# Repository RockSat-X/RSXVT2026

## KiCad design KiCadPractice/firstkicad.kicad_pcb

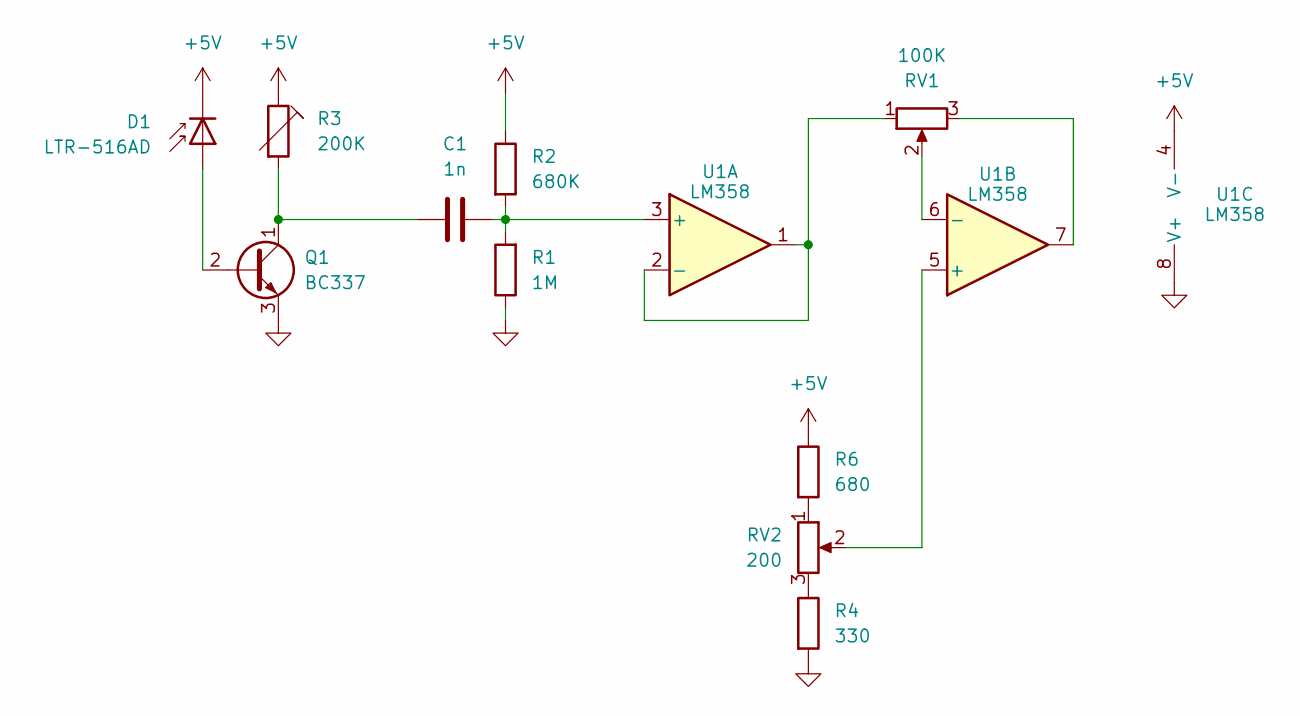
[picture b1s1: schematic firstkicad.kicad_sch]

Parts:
C1: 1n; C_1206_3216Metric_Pad1.33x1.80mm_HandSolder
D1: LTR-516AD
Q1: BC337; TO-92L_Inline
R1: 1M; R_1206_3216Metric_Pad1.30x1.75mm_HandSolder
R2: 680K; R_1206_3216Metric_Pad1.30x1.75mm_HandSolder
R3: 200K; R_1206_3216Metric_Pad1.30x1.75mm_HandSolder
R4: 330; R_1206_3216Metric_Pad1.30x1.75mm_HandSolder
R6: 680; R_1206_3216Metric_Pad1.30x1.75mm_HandSolder
RV1: 100K; Potentiometer_Bourns_3266W_Vertical
RV2: 200; Potentiometer_Bourns_3266W_Vertical
U1: LM358; SOT-23-8_Handsoldering

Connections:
+5V: D1.1 (K), R2.1, R3.1, R6.1, U1.4 (V-)
GND: Q1.3 (E), R1.1, R4.2, U1.8 (V+)
unnamed: D1.2 (A), Q1.2 (B)
unnamed: C1.1, Q1.1 (C), R3.2
unnamed: R4.1, RV2.3
unnamed: R6.2, RV2.1
unnamed: RV1.3, U1.7
unnamed: C1.2, R1.2, R2.2, U1.3 (+)
unnamed: RV1.1, U1.1, U1.2 (-)
unnamed: RV2.2, U1.5 (+)
unnamed: RV1.2, U1.6 (-)

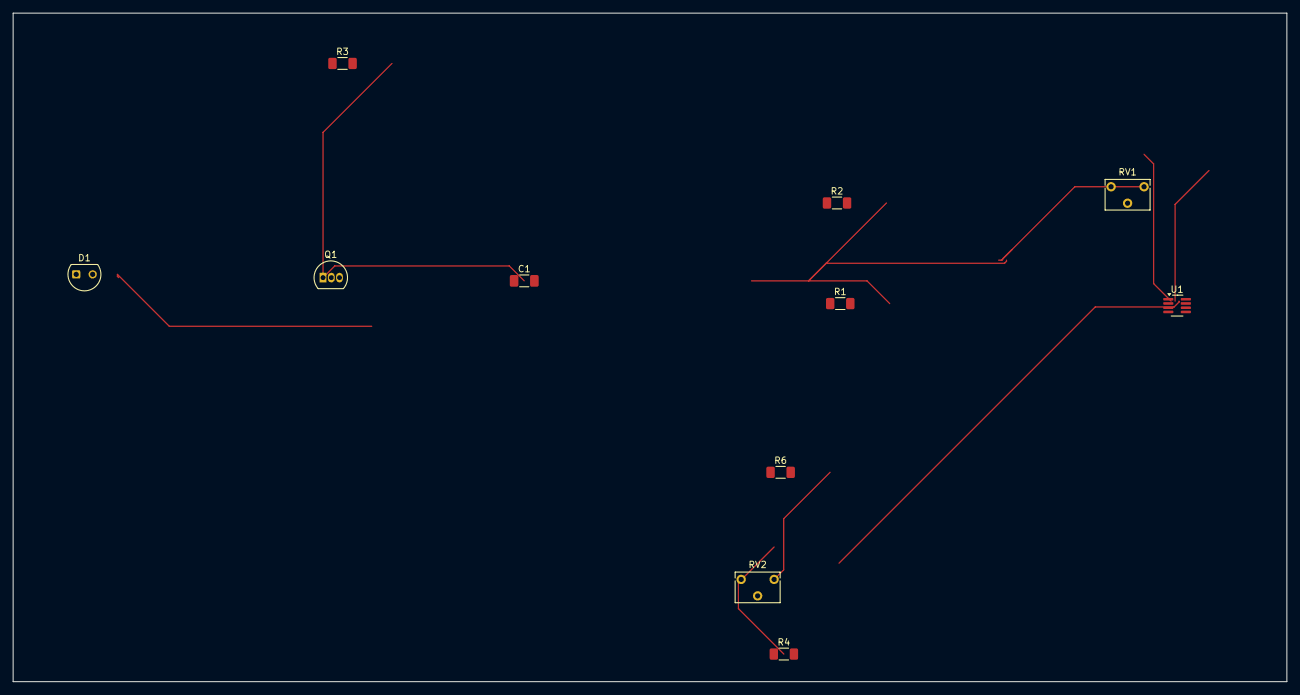
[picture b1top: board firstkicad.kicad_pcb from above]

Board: 2 copper layers, 196.2 x 103.0 mm, 11 parts (0 on the bottom side), 11 nets.

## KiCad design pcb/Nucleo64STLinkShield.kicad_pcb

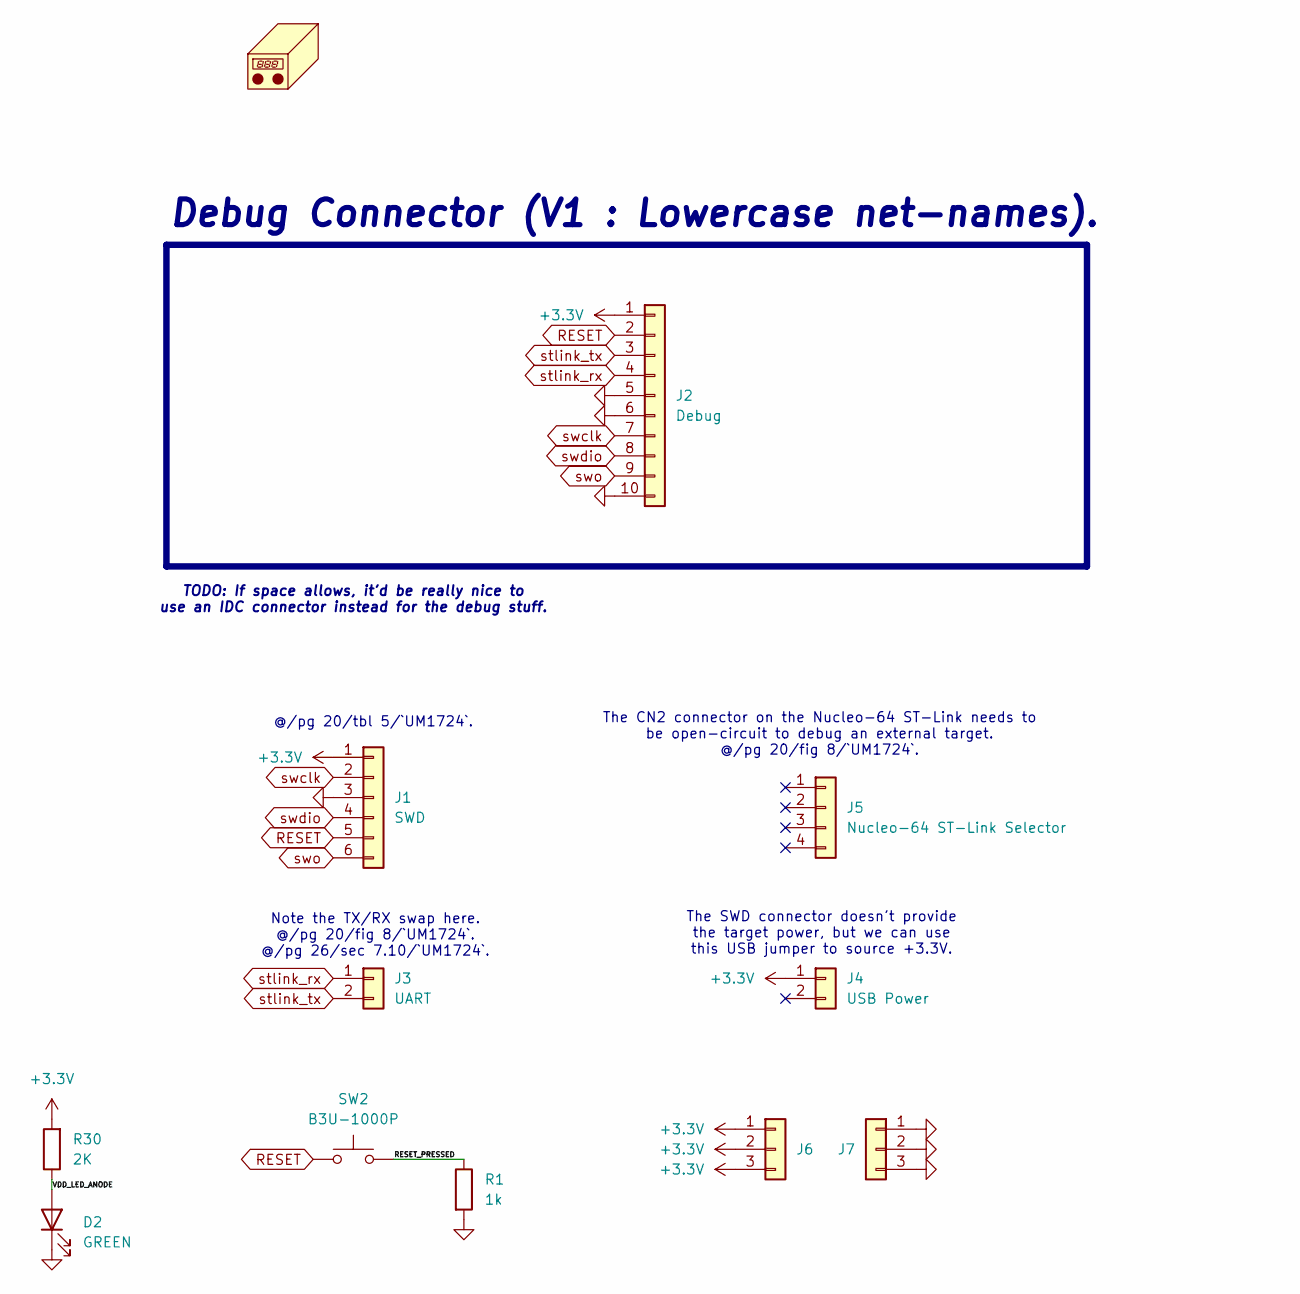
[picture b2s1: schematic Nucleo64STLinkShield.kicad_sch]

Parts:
D2: GREEN; LED_1206_3216Metric_Pad1.42x1.75mm_HandSolder
J1: SWD; PinSocket_1x06_P2.54mm_Vertical
J2: Debug; Molex_PicoBlade_53047-1010_1x10_P1.25mm_Vertical
J3: UART; PinSocket_1x02_P2.54mm_Vertical
J4: USB Power; PinSocket_1x02_P2.54mm_Vertical
J5: Nucleo-64 ST-Link Selector; PinSocket_1x04_P2.54mm_Vertical
J6, J7: Conn_01x03; PinHeader_1x03_P2.54mm_Vertical
N1: Housing; Nucleo64STLinkShieldHousing
R1: 1k; R_1206_3216Metric_Pad1.30x1.75mm_HandSolder
R30: 2K; R_1206_3216Metric_Pad1.30x1.75mm_HandSolder
SW2: B3U-1000P; SW_SPST_B3U-1000P

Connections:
+3.3V: J1.1, J2.1, J4.1, J6.1, J6.2, J6.3, R30.2
/RESET_PRESSED: R1.1, SW2.1
/VDD_LED_ANODE: D2.2 (A), R30.1
GND: D2.1 (K), J1.3, J2.5, J2.6, J2.10, J7.1, J7.2, J7.3, R1.2
RESET: J1.5, J2.2, SW2.2
stlink_rx: J2.4, J3.1
stlink_tx: J2.3, J3.2
swclk: J1.2, J2.7
swdio: J1.4, J2.8
swo: J1.6, J2.9

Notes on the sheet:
The CN2 connector on the Nucleo-64 ST-Link needs to be open-circuit to debug an external target. @/pg 20/fig 8/`UM1724`.
Debug Connector (V1 : Lowercase net-names).
Note the TX/RX swap here. @/pg 20/fig 8/`UM1724`. @/pg 26/sec 7.10/`UM1724`.
The SWD connector doesn't provide the target power, but we can use this USB jumper to source +3.3V.
TODO: If space allows, it'd be really nice to use an IDC connector instead for the debug stuff.
@/pg 20/tbl 5/`UM1724`.

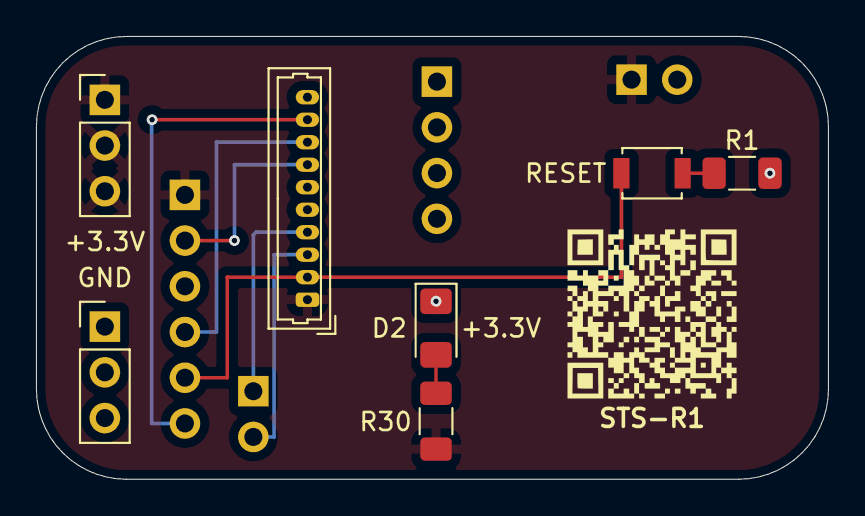
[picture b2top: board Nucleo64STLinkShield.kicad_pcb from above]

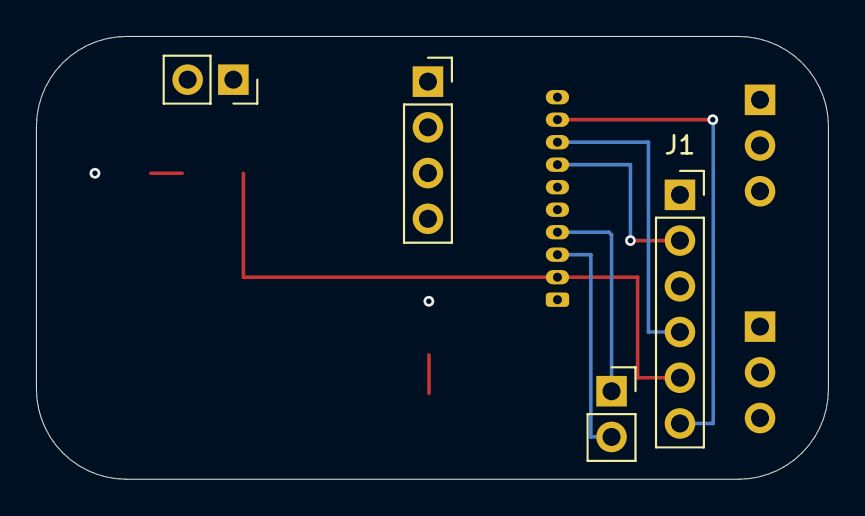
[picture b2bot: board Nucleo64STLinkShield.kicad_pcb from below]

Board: 4 copper layers, 44.0 x 24.6 mm, 12 parts (4 on the bottom side), 10 nets.

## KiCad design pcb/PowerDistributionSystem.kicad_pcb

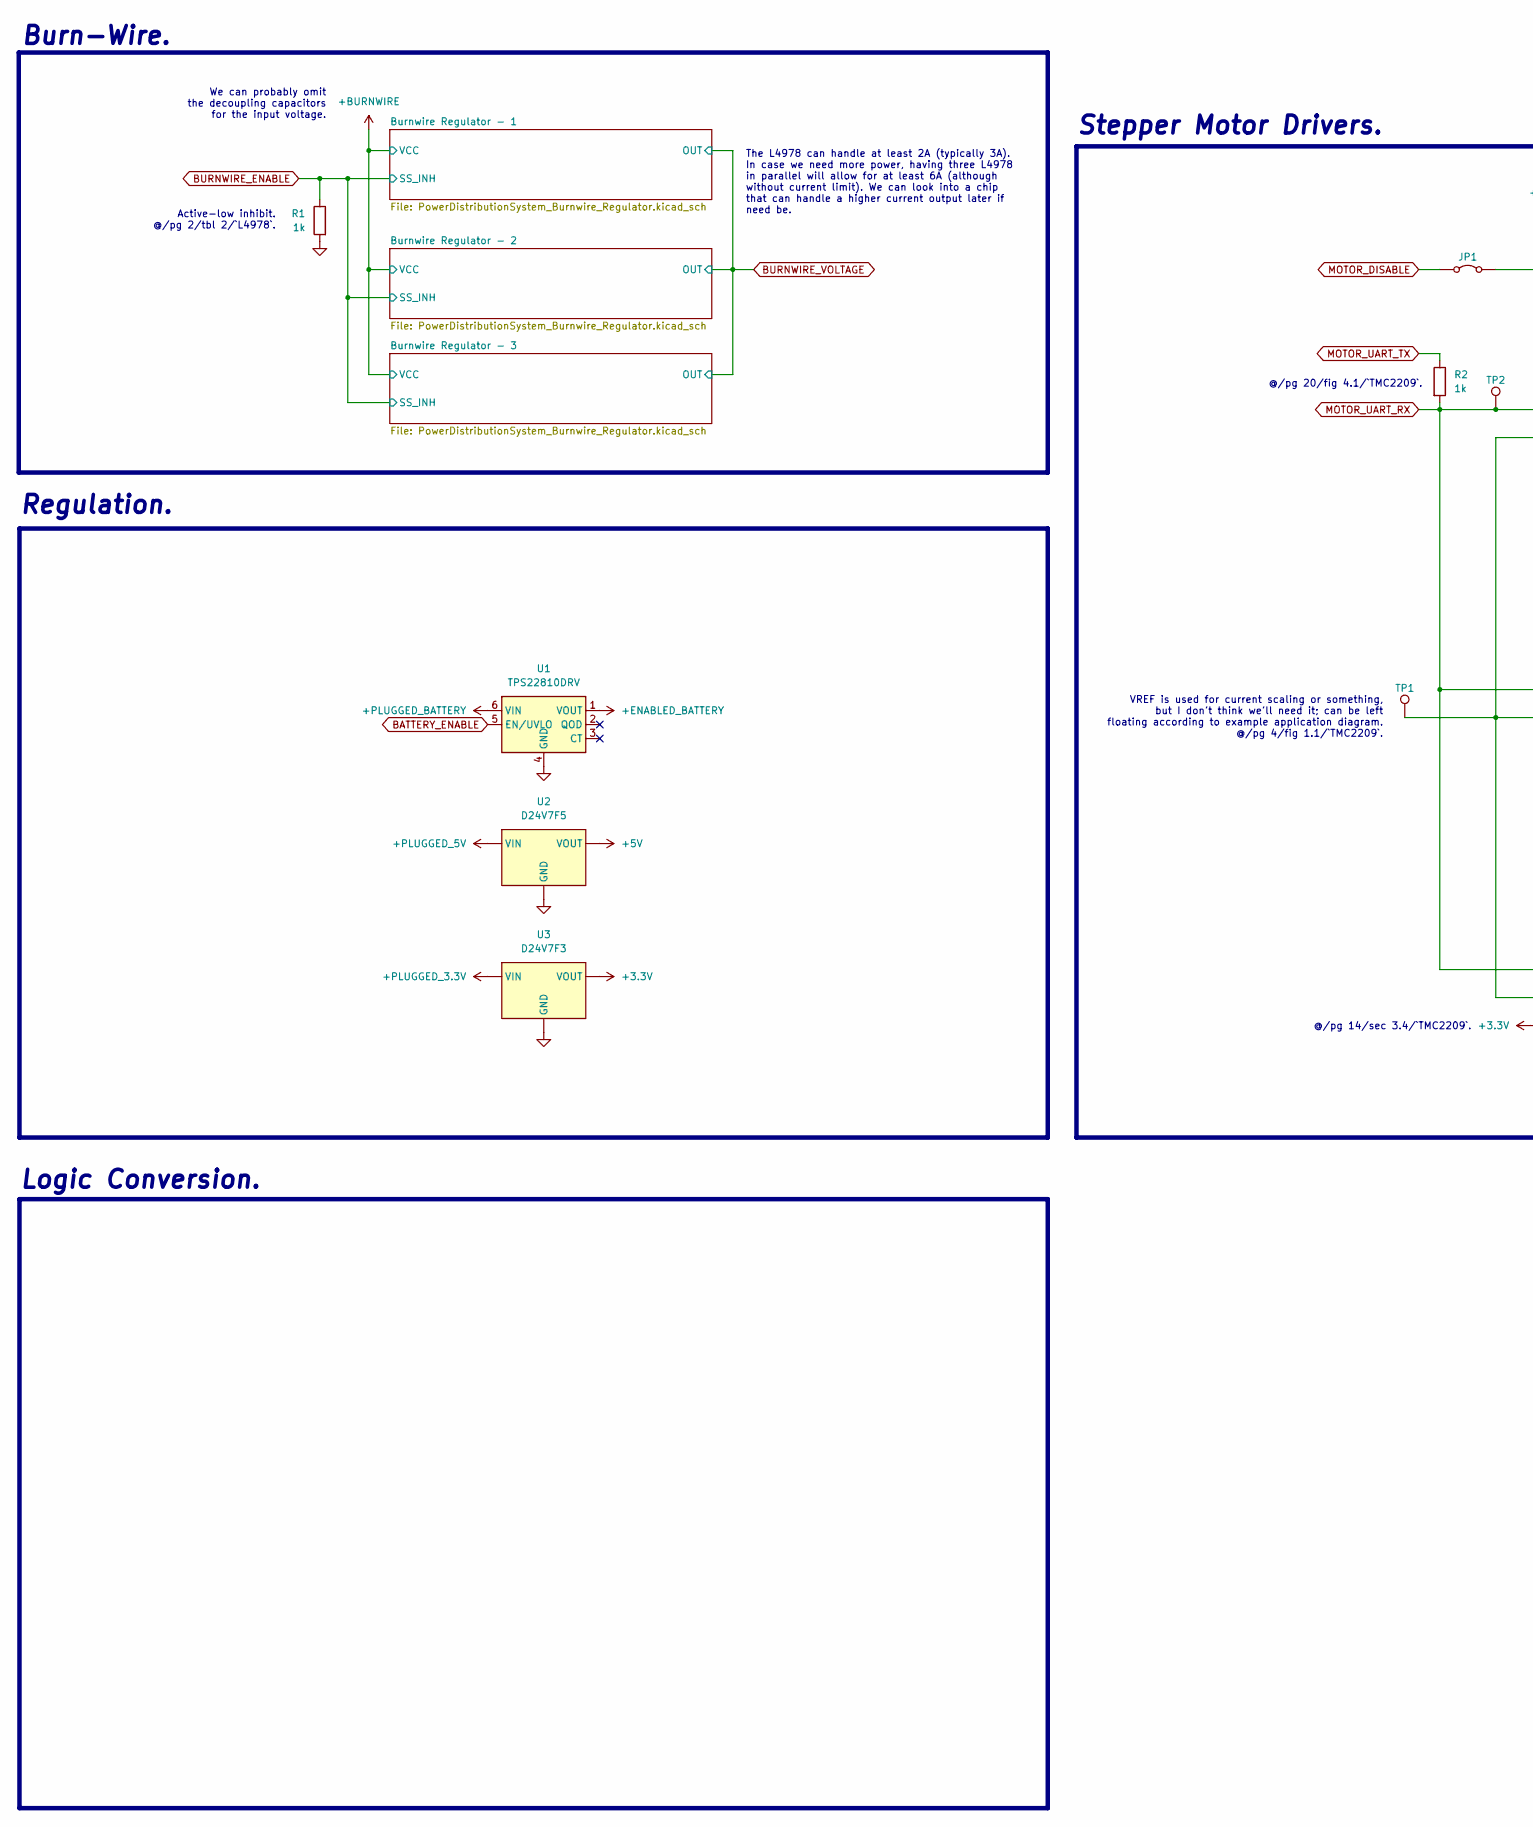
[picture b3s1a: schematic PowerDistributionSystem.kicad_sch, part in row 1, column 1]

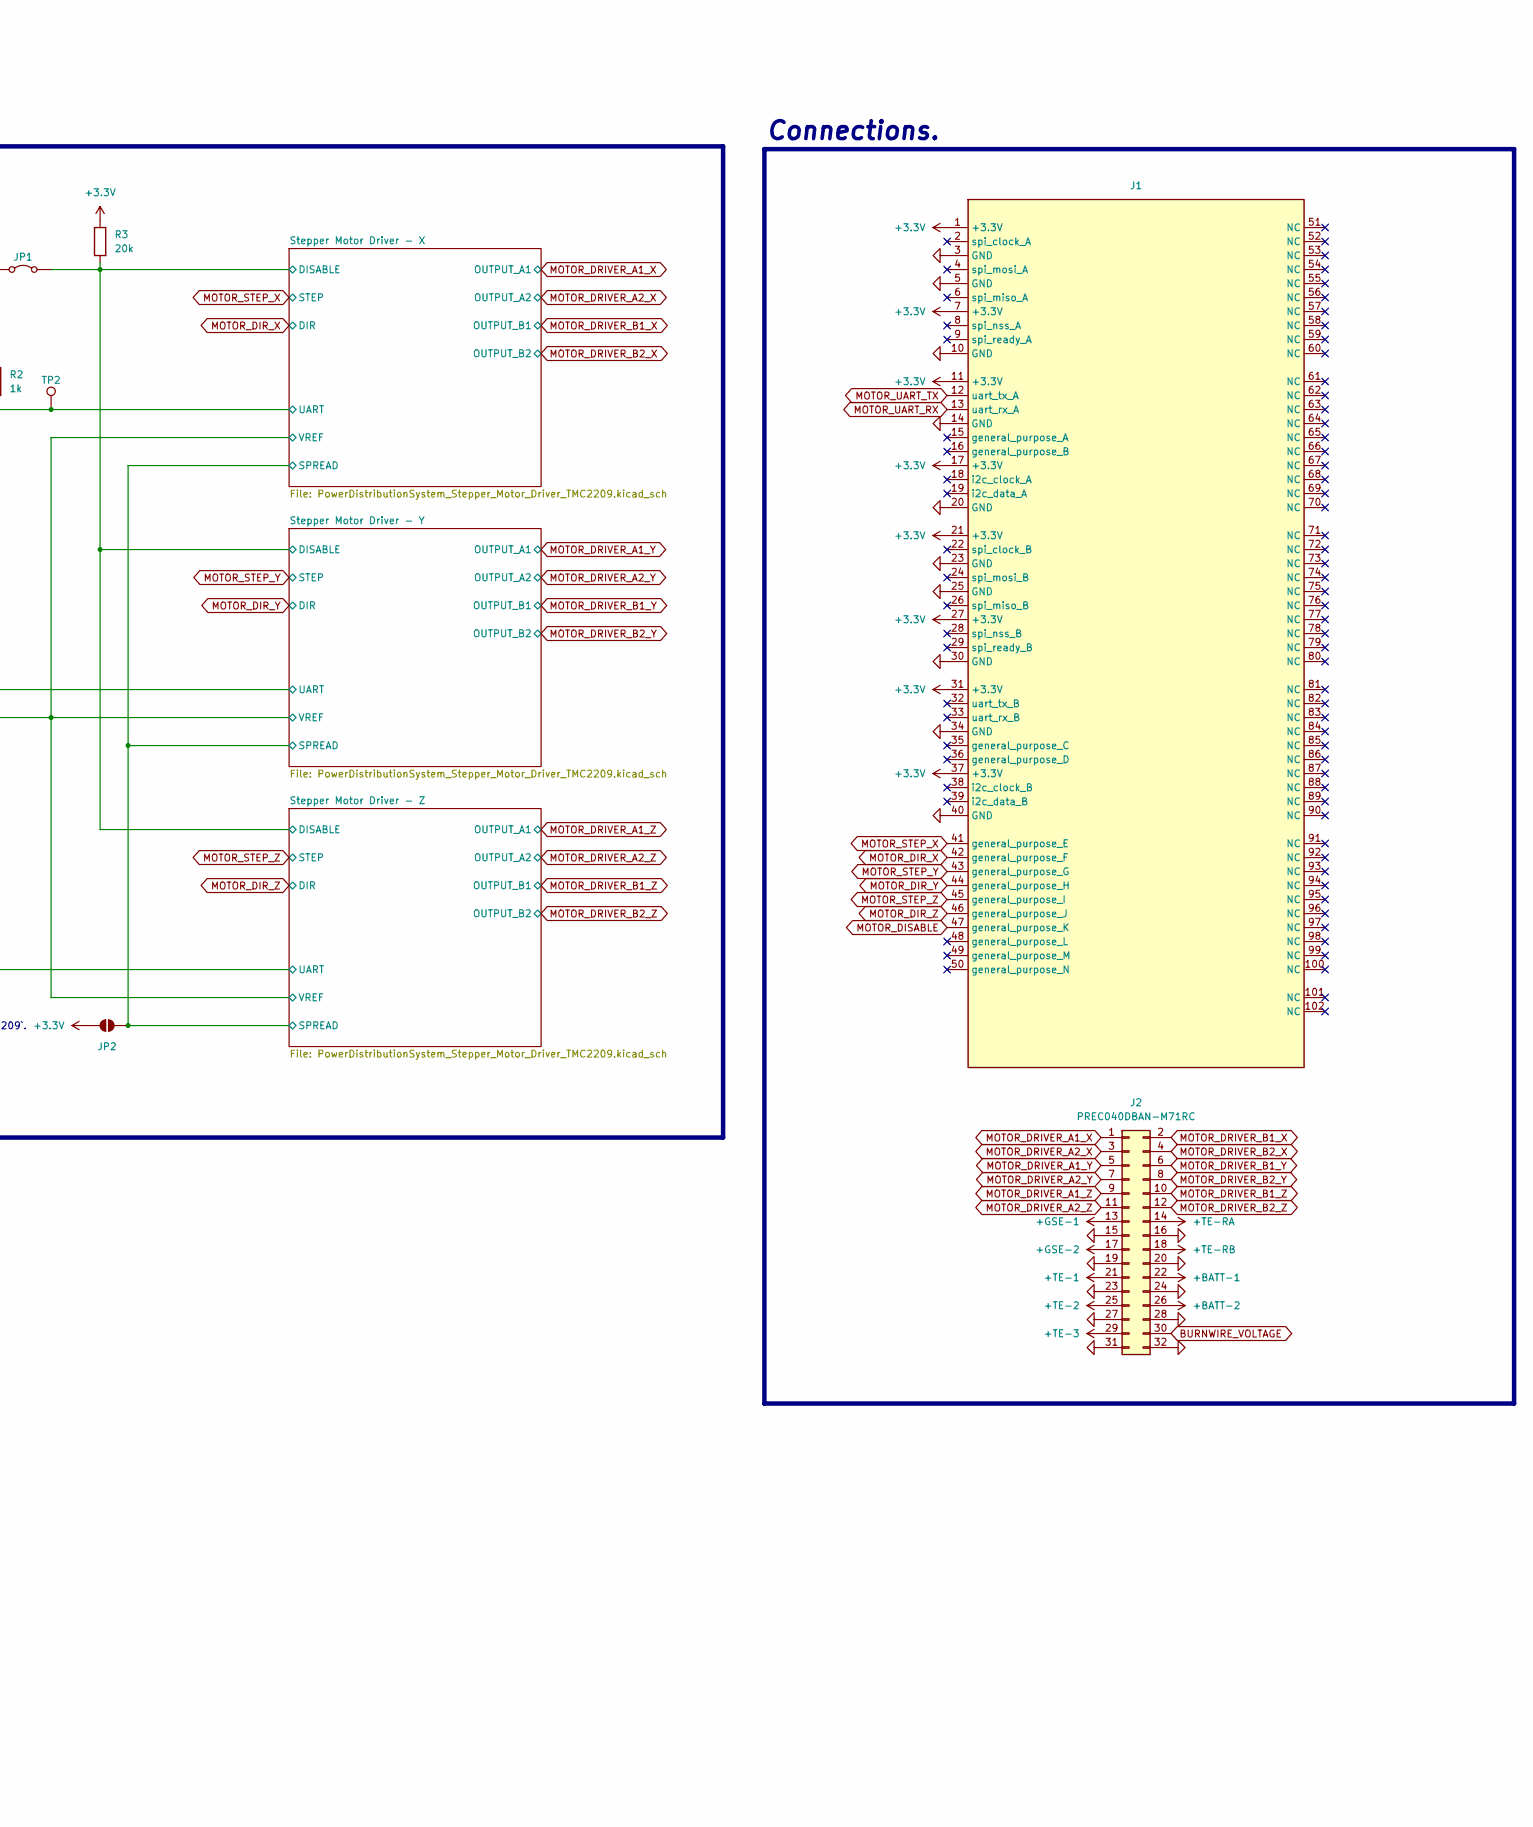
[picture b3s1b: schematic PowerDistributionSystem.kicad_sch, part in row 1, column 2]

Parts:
J1: StackConnector
J2: PREC040DBAN-M71RC; PinHeader_2x16_P2.54mm_Horizontal
JP1: Jumper_2_Bridged; SolderJumper-2_P1.3mm_Open_RoundedPad1.0x1.5mm
JP2: SolderJumper_2_Open; SolderJumper-2_P1.3mm_Open_RoundedPad1.0x1.5mm
R1, R2: 1k; R_1206_3216Metric_Pad1.30x1.75mm_HandSolder
R3: 20k; R_1206_3216Metric_Pad1.30x1.75mm_HandSolder
TP1, TP2: TestPoint; TestPoint_Pad_1.0x1.0mm
U1: TPS22810DRV; WSON-6-1EP_2x2mm_P0.65mm_EP1x1.6mm
U2: D24V7F5; D24V7Fx
U3: D24V7F3; D24V7Fx

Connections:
+3.3V: J1.1 (+3.3V), J1.7 (+3.3V), J1.11 (+3.3V), J1.17 (+3.3V), J1.21 (+3.3V), J1.27 (+3.3V), J1.31 (+3.3V), J1.37 (+3.3V), JP2.1 (A), R3.1, U3.VOUT; also elsewhere on the board
+5V: U2.VOUT
+BATT-1: J2.22
+BATT-2: J2.26
+ENABLED_BATTERY: U1.1 (VOUT)
+GSE-1: J2.13
+GSE-2: J2.17
+PLUGGED_3.3V: U3.VIN
+PLUGGED_5V: U2.VIN
+PLUGGED_BATTERY: U1.6 (VIN)
+TE-1: J2.21
+TE-2: J2.25
+TE-3: J2.29
+TE-RA: J2.14
+TE-RB: J2.18
/Stepper Motor Driver - X/DISABLE: JP1.2 (B), R3.2; also elsewhere on the board
/Stepper Motor Driver - X/SPREAD: JP2.2 (B); also elsewhere on the board
/Stepper Motor Driver - X/VREF: TP1.1; also elsewhere on the board
BATTERY_ENABLE: U1.5 (EN/UVLO)
BURNWIRE_ENABLE: R1.1; also elsewhere on the board
BURNWIRE_VOLTAGE: J2.30; also elsewhere on the board
GND: J1.3 (GND), J1.5 (GND), J1.10 (GND), J1.14 (GND), J1.20 (GND), J1.23 (GND), J1.25 (GND), J1.30 (GND), J1.34 (GND), J1.40 (GND), J2.15, J2.16, J2.19, J2.20, J2.23, J2.24, J2.27, J2.28, J2.31, J2.32, R1.2, U1.4 (GND), U1.7 (GND), U2.GND, U3.GND; also elsewhere on the board
MOTOR_DIR_X: J1.42 (general_purpose_F); also elsewhere on the board
MOTOR_DIR_Y: J1.44 (general_purpose_H); also elsewhere on the board
MOTOR_DIR_Z: J1.46 (general_purpose_J); also elsewhere on the board
MOTOR_DISABLE: J1.47 (general_purpose_K), JP1.1 (A)
MOTOR_DRIVER_A1_X: J2.1; also elsewhere on the board
MOTOR_DRIVER_A1_Y: J2.5; also elsewhere on the board
MOTOR_DRIVER_A1_Z: J2.9; also elsewhere on the board
MOTOR_DRIVER_A2_X: J2.3; also elsewhere on the board
MOTOR_DRIVER_A2_Y: J2.7; also elsewhere on the board
MOTOR_DRIVER_A2_Z: J2.11; also elsewhere on the board
MOTOR_DRIVER_B1_X: J2.2; also elsewhere on the board
MOTOR_DRIVER_B1_Y: J2.6; also elsewhere on the board
MOTOR_DRIVER_B1_Z: J2.10; also elsewhere on the board
MOTOR_DRIVER_B2_X: J2.4; also elsewhere on the board
MOTOR_DRIVER_B2_Y: J2.8; also elsewhere on the board
MOTOR_DRIVER_B2_Z: J2.12; also elsewhere on the board
MOTOR_STEP_X: J1.41 (general_purpose_E); also elsewhere on the board
MOTOR_STEP_Y: J1.43 (general_purpose_G); also elsewhere on the board
MOTOR_STEP_Z: J1.45 (general_purpose_I); also elsewhere on the board
MOTOR_UART_RX: J1.13 (uart_rx_A), R2.2, TP2.1; also elsewhere on the board
MOTOR_UART_TX: J1.12 (uart_tx_A), R2.1

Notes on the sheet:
Active-low inhibit. @/pg 2/tbl 2/`L4978`.
Connections.
The L4978 can handle at least 2A (typically 3A). In case we need more power, having three L4978 in parallel will allow for at least 6A (although without current limit). We can look into a chip that can handle a higher current output later if need be.
Burn-Wire.
Regulation.
We can probably omit the decoupling capacitors for the input voltage.
@/pg 20/fig 4.1/`TMC2209`.
Logic Conversion.
Stepper Motor Drivers.
VREF is used for current scaling or something, but I don't think we'll need it; can be left floating according to example application diagram. @/pg 4/fig 1.1/`TMC2209`.
@/pg 14/sec 3.4/`TMC2209`.

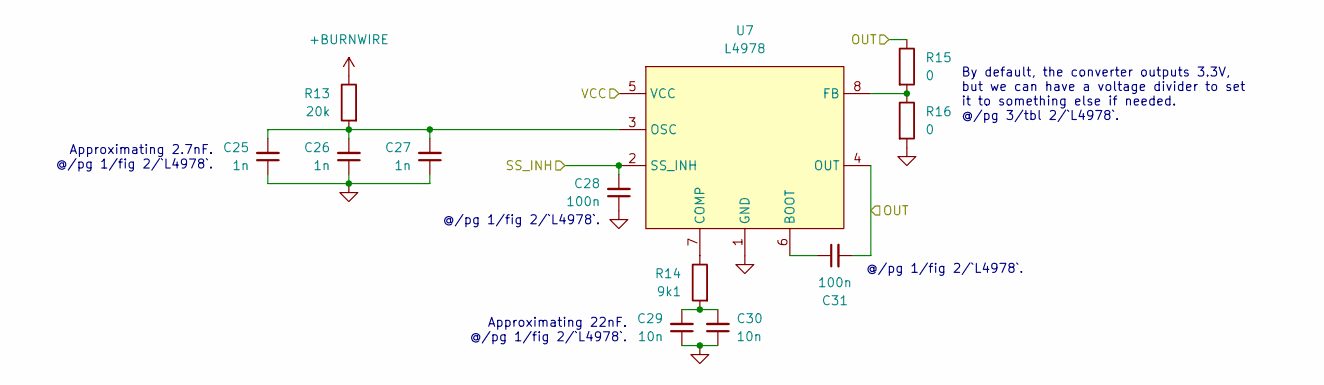
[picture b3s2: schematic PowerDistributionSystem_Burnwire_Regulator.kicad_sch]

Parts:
C25, C26, C27: 1n; C_1206_3216Metric_Pad1.33x1.80mm_HandSolder
C28, C31: 100n; C_1206_3216Metric_Pad1.33x1.80mm_HandSolder
C29, C30: 10n; C_1206_3216Metric_Pad1.33x1.80mm_HandSolder
R13: 20k; R_1206_3216Metric_Pad1.30x1.75mm_HandSolder
R14: 9k1; R_1206_3216Metric_Pad1.30x1.75mm_HandSolder
R15, R16: 0; R_1206_3216Metric_Pad1.30x1.75mm_HandSolder
U7: L4978; DIP-8_W7.62mm

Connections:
+BURNWIRE: R13.1, U7.5 (VCC); also elsewhere on the board
BURNWIRE_ENABLE: C28.2, U7.2 (SS_INH); also elsewhere on the board
BURNWIRE_VOLTAGE: C31.2, R15.1, U7.4 (OUT); also elsewhere on the board
GND: C25.1, C26.1, C27.1, C28.1, C29.1, C30.1, R16.2, U7.1 (GND); also elsewhere on the board
unnamed: C29.2, C30.2, R14.2
unnamed: C31.1, U7.6 (BOOT)
unnamed: R14.1, U7.7 (COMP)
unnamed: R15.2, R16.1, U7.8 (FB)
unnamed: C25.2, C26.2, C27.2, R13.2, U7.3 (OSC)

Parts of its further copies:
C32, C33, C34: 1n; C_1206_3216Metric_Pad1.33x1.80mm_HandSolder
C35, C38: 100n; C_1206_3216Metric_Pad1.33x1.80mm_HandSolder
C36, C37: 10n; C_1206_3216Metric_Pad1.33x1.80mm_HandSolder
R17: 20k; R_1206_3216Metric_Pad1.30x1.75mm_HandSolder
R18: 9k1; R_1206_3216Metric_Pad1.30x1.75mm_HandSolder
R19, R20: 0; R_1206_3216Metric_Pad1.30x1.75mm_HandSolder
U8: L4978; DIP-8_W7.62mm

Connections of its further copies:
+BURNWIRE: R17.1, U8.5 (VCC); also elsewhere on the board
BURNWIRE_ENABLE: C35.2, U8.2 (SS_INH); also elsewhere on the board
BURNWIRE_VOLTAGE: C38.2, R19.1, U8.4 (OUT); also elsewhere on the board
GND: C32.1, C33.1, C34.1, C35.1, C36.1, C37.1, R20.2, U8.1 (GND); also elsewhere on the board
unnamed: C36.2, C37.2, R18.2
unnamed: C38.1, U8.6 (BOOT)
unnamed: R18.1, U8.7 (COMP)
unnamed: R19.2, R20.1, U8.8 (FB)
unnamed: C32.2, C33.2, C34.2, R17.2, U8.3 (OSC)

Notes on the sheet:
Approximating 22nF. @/pg 1/fig 2/`L4978`.
Approximating 2.7nF. @/pg 1/fig 2/`L4978`.
By default, the converter outputs 3.3V, but we can have a voltage divider to set it to something else if needed. @/pg 3/tbl 2/`L4978`.
@/pg 1/fig 2/`L4978`.

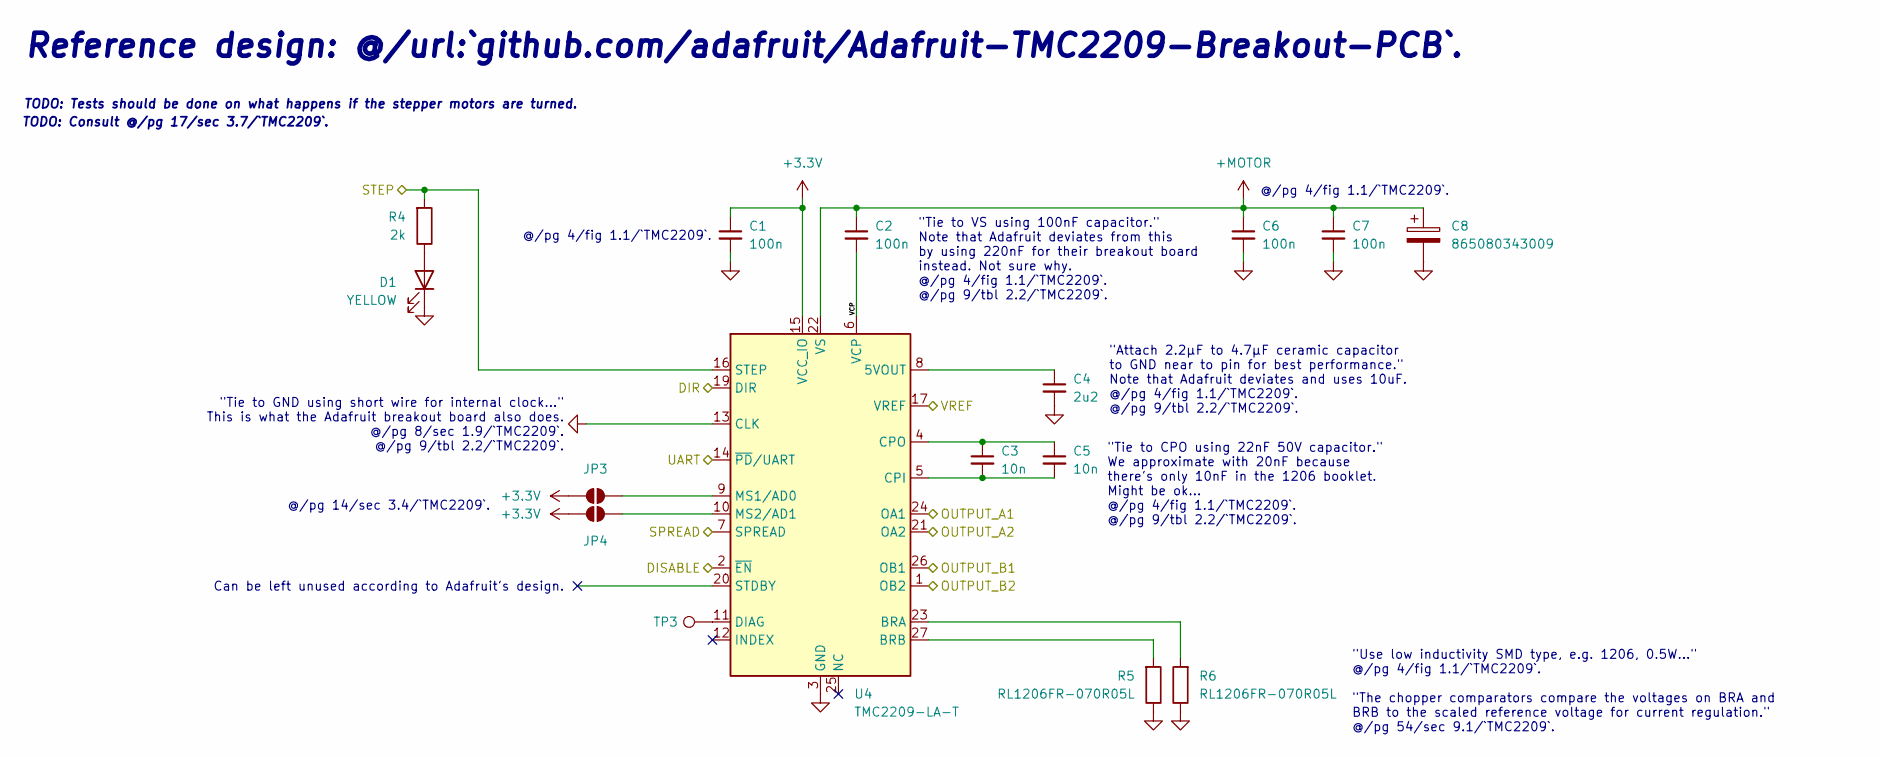
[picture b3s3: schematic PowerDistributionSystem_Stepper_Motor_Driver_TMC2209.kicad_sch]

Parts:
C1, C2, C6, C7: 100n; C_1206_3216Metric_Pad1.33x1.80mm_HandSolder
C3, C5: 10n; C_1206_3216Metric_Pad1.33x1.80mm_HandSolder
C4: 2u2; C_1206_3216Metric_Pad1.33x1.80mm_HandSolder
C8: 865080343009; CP_Elec_6.3x5.4
D1: YELLOW; LED_1206_3216Metric_Pad1.42x1.75mm_HandSolder
JP3, JP4: SolderJumper_2_Open; SolderJumper-2_P1.3mm_Open_RoundedPad1.0x1.5mm
R4: 2k; R_1206_3216Metric_Pad1.30x1.75mm_HandSolder
R5, R6: RL1206FR-070R05L; R_1206_3216Metric_Pad1.30x1.75mm_HandSolder
TP3: TestPoint; TestPoint_Pad_1.0x1.0mm
U4: TMC2209-LA-T; VQFN-28-1EP_5x5mm_P0.5mm_EP3.7x3.7mm_ThermalVias

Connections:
+3.3V: C1.1, JP3.1 (A), JP4.1 (A), U4.15 (VCC_IO); also elsewhere on the board
+MOTOR: C2.1, C6.1, C7.1, C8.1, U4.22 (VS), U4.28 (VS); also elsewhere on the board
/Stepper Motor Driver - X/DISABLE: U4.2 (~EN); also elsewhere on the board
/Stepper Motor Driver - X/SPREAD: U4.7 (SPREAD); also elsewhere on the board
/Stepper Motor Driver - X/VCP: C2.2, U4.6 (VCP)
/Stepper Motor Driver - X/VREF: U4.17 (VREF); also elsewhere on the board
GND: C1.2, C4.2, C6.2, C7.2, C8.2, D1.1 (K), R5.1, R6.1, U4.3 (GND), U4.13 (CLK), U4.18 (GND), U4.29 (GND); also elsewhere on the board
MOTOR_DIR_X: U4.19 (DIR); also elsewhere on the board
MOTOR_DRIVER_A1_X: U4.24 (OA1); also elsewhere on the board
MOTOR_DRIVER_A2_X: U4.21 (OA2); also elsewhere on the board
MOTOR_DRIVER_B1_X: U4.26 (OB1); also elsewhere on the board
MOTOR_DRIVER_B2_X: U4.1 (OB2); also elsewhere on the board
MOTOR_STEP_X: R4.2, U4.16 (STEP); also elsewhere on the board
MOTOR_UART_RX: U4.14 (~PD/UART); also elsewhere on the board
unnamed: D1.2 (A), R4.1
unnamed: JP3.2 (B), U4.9 (MS1/AD0)
unnamed: JP4.2 (B), U4.10 (MS2/AD1)
unnamed: C4.1, U4.8 (5VOUT)
unnamed: R6.2, U4.23 (BRA)
unnamed: R5.2, U4.27 (BRB)
unnamed: C3.2, C5.2, U4.5 (CPI)
unnamed: C3.1, C5.1, U4.4 (CPO)
unnamed: TP3.1, U4.11 (DIAG)

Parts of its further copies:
C9, C10, C14, C15, C17, C18, C22, C23: 100n; C_1206_3216Metric_Pad1.33x1.80mm_HandSolder
C11, C13, C19, C21: 10n; C_1206_3216Metric_Pad1.33x1.80mm_HandSolder
C12, C20: 2u2; C_1206_3216Metric_Pad1.33x1.80mm_HandSolder
C16, C24: 865080343009; CP_Elec_6.3x5.4
D2, D3: YELLOW; LED_1206_3216Metric_Pad1.42x1.75mm_HandSolder
JP5, JP6, JP7, JP8: SolderJumper_2_Open; SolderJumper-2_P1.3mm_Open_RoundedPad1.0x1.5mm
R7, R10: 2k; R_1206_3216Metric_Pad1.30x1.75mm_HandSolder
R8, R9, R11, R12: RL1206FR-070R05L; R_1206_3216Metric_Pad1.30x1.75mm_HandSolder
TP4, TP5: TestPoint; TestPoint_Pad_1.0x1.0mm
U5, U6: TMC2209-LA-T; VQFN-28-1EP_5x5mm_P0.5mm_EP3.7x3.7mm_ThermalVias

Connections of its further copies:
+3.3V: C9.1, C17.1, JP5.1 (A), JP6.1 (A), JP7.1 (A), JP8.1 (A), U5.15 (VCC_IO), U6.15 (VCC_IO); also elsewhere on the board
+MOTOR: C10.1, C14.1, C15.1, C16.1, C18.1, C22.1, C23.1, C24.1, U5.22 (VS), U5.28 (VS), U6.22 (VS), U6.28 (VS); also elsewhere on the board
/Stepper Motor Driver - X/DISABLE: U5.2 (~EN), U6.2 (~EN); also elsewhere on the board
/Stepper Motor Driver - X/SPREAD: U5.7 (SPREAD), U6.7 (SPREAD); also elsewhere on the board
/Stepper Motor Driver - X/VREF: U5.17 (VREF), U6.17 (VREF); also elsewhere on the board
/Stepper Motor Driver - Y/VCP: C10.2, U5.6 (VCP)
/Stepper Motor Driver - Z/VCP: C18.2, U6.6 (VCP)
GND: C9.2, C12.2, C14.2, C15.2, C16.2, C17.2, C20.2, C22.2, C23.2, C24.2, D2.1 (K), D3.1 (K), R8.1, R9.1, R11.1, R12.1, U5.3 (GND), U5.13 (CLK), U5.18 (GND), U5.29 (GND), U6.3 (GND), U6.13 (CLK), U6.18 (GND), U6.29 (GND); also elsewhere on the board
MOTOR_DIR_Y: U5.19 (DIR); also elsewhere on the board
MOTOR_DIR_Z: U6.19 (DIR); also elsewhere on the board
MOTOR_DRIVER_A1_Y: U5.24 (OA1); also elsewhere on the board
MOTOR_DRIVER_A1_Z: U6.24 (OA1); also elsewhere on the board
MOTOR_DRIVER_A2_Y: U5.21 (OA2); also elsewhere on the board
MOTOR_DRIVER_A2_Z: U6.21 (OA2); also elsewhere on the board
MOTOR_DRIVER_B1_Y: U5.26 (OB1); also elsewhere on the board
MOTOR_DRIVER_B1_Z: U6.26 (OB1); also elsewhere on the board
MOTOR_DRIVER_B2_Y: U5.1 (OB2); also elsewhere on the board
MOTOR_DRIVER_B2_Z: U6.1 (OB2); also elsewhere on the board
MOTOR_STEP_Y: R7.2, U5.16 (STEP); also elsewhere on the board
MOTOR_STEP_Z: R10.2, U6.16 (STEP); also elsewhere on the board
MOTOR_UART_RX: U5.14 (~PD/UART), U6.14 (~PD/UART); also elsewhere on the board
unnamed: D2.2 (A), R7.1
unnamed: D3.2 (A), R10.1
unnamed: JP5.2 (B), U5.9 (MS1/AD0)
unnamed: JP6.2 (B), U5.10 (MS2/AD1)
unnamed: JP7.2 (B), U6.9 (MS1/AD0)
unnamed: JP8.2 (B), U6.10 (MS2/AD1)
unnamed: C12.1, U5.8 (5VOUT)
unnamed: R9.2, U5.23 (BRA)
unnamed: R8.2, U5.27 (BRB)
unnamed: C11.2, C13.2, U5.5 (CPI)
unnamed: C11.1, C13.1, U5.4 (CPO)
unnamed: TP4.1, U5.11 (DIAG)
unnamed: C20.1, U6.8 (5VOUT)
unnamed: R12.2, U6.23 (BRA)
unnamed: R11.2, U6.27 (BRB)
unnamed: C19.2, C21.2, U6.5 (CPI)
unnamed: C19.1, C21.1, U6.4 (CPO)
unnamed: TP5.1, U6.11 (DIAG)

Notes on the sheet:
"Use low inductivity SMD type, e.g. 1206, 0.5W..." @/pg 4/fig 1.1/`TMC2209`. "The chopper comparators compare the voltages on BRA and BRB to the scaled reference voltage for current regulation." @/pg 54/sec 9.1/`TMC2209`.
TODO: Tests should be done on what happens if the stepper motors are turned.
"Tie to VS using 100nF capacitor." Note that Adafruit deviates from this by using 220nF for their breakout board instead. Not sure why. @/pg 4/fig 1.1/`TMC2209`. @/pg 9/tbl 2.2/`TMC2209`.
@/pg 14/sec 3.4/`TMC2209`.
"Tie to CPO using 22nF 50V capacitor." We approximate with 20nF because there's only 10nF in the 1206 booklet. Might be ok... @/pg 4/fig 1.1/`TMC2209`. @/pg 9/tbl 2.2/`TMC2209`.
@/pg 4/fig 1.1/`TMC2209`.
Reference design: @/url:`github.com/adafruit/Adafruit-TMC2209-Breakout-PCB`.
"Attach 2.2μF to 4.7μF ceramic capacitor to GND near to pin for best performance." Note that Adafruit deviates and uses 10uF. @/pg 4/fig 1.1/`TMC2209`. @/pg 9/tbl 2.2/`TMC2209`.
"Tie to GND using short wire for internal clock..." This is what the Adafruit breakout board also does. @/pg 8/sec 1.9/`TMC2209`. @/pg 9/tbl 2.2/`TMC2209`.
TODO: Consult @/pg 17/sec 3.7/`TMC2209`.
Can be left unused according to Adafruit's design.

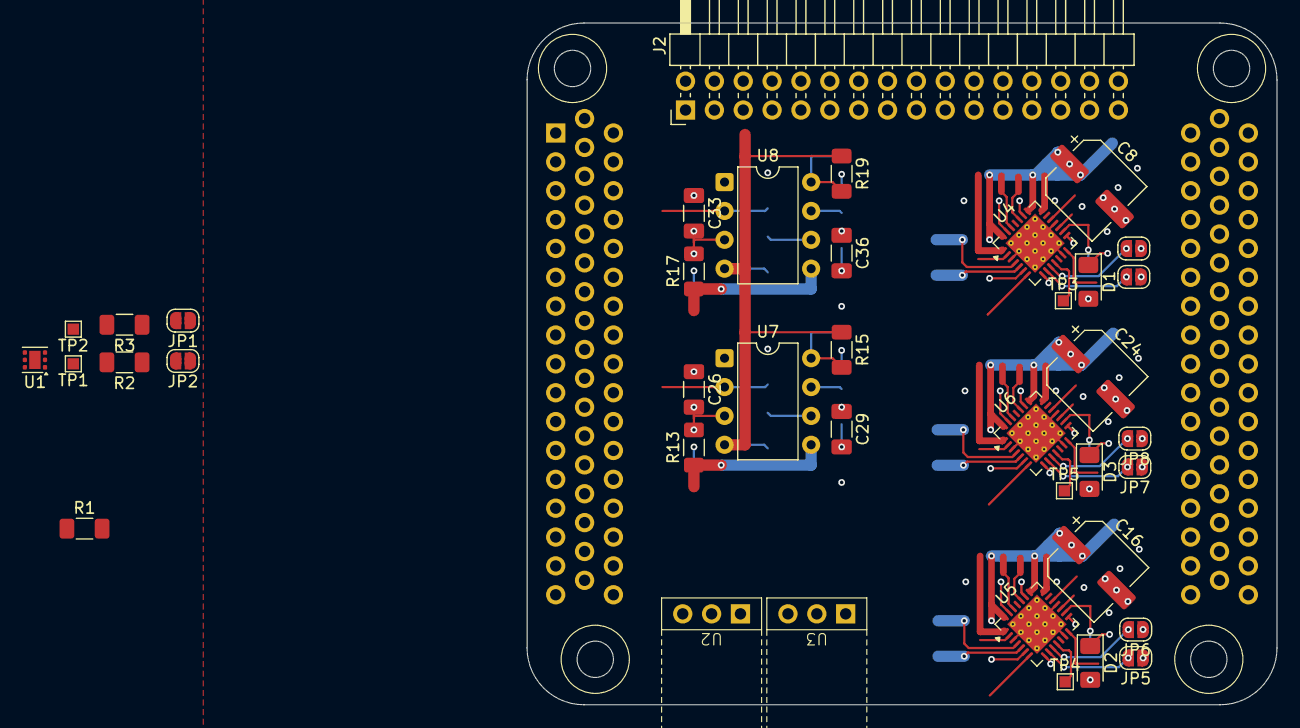
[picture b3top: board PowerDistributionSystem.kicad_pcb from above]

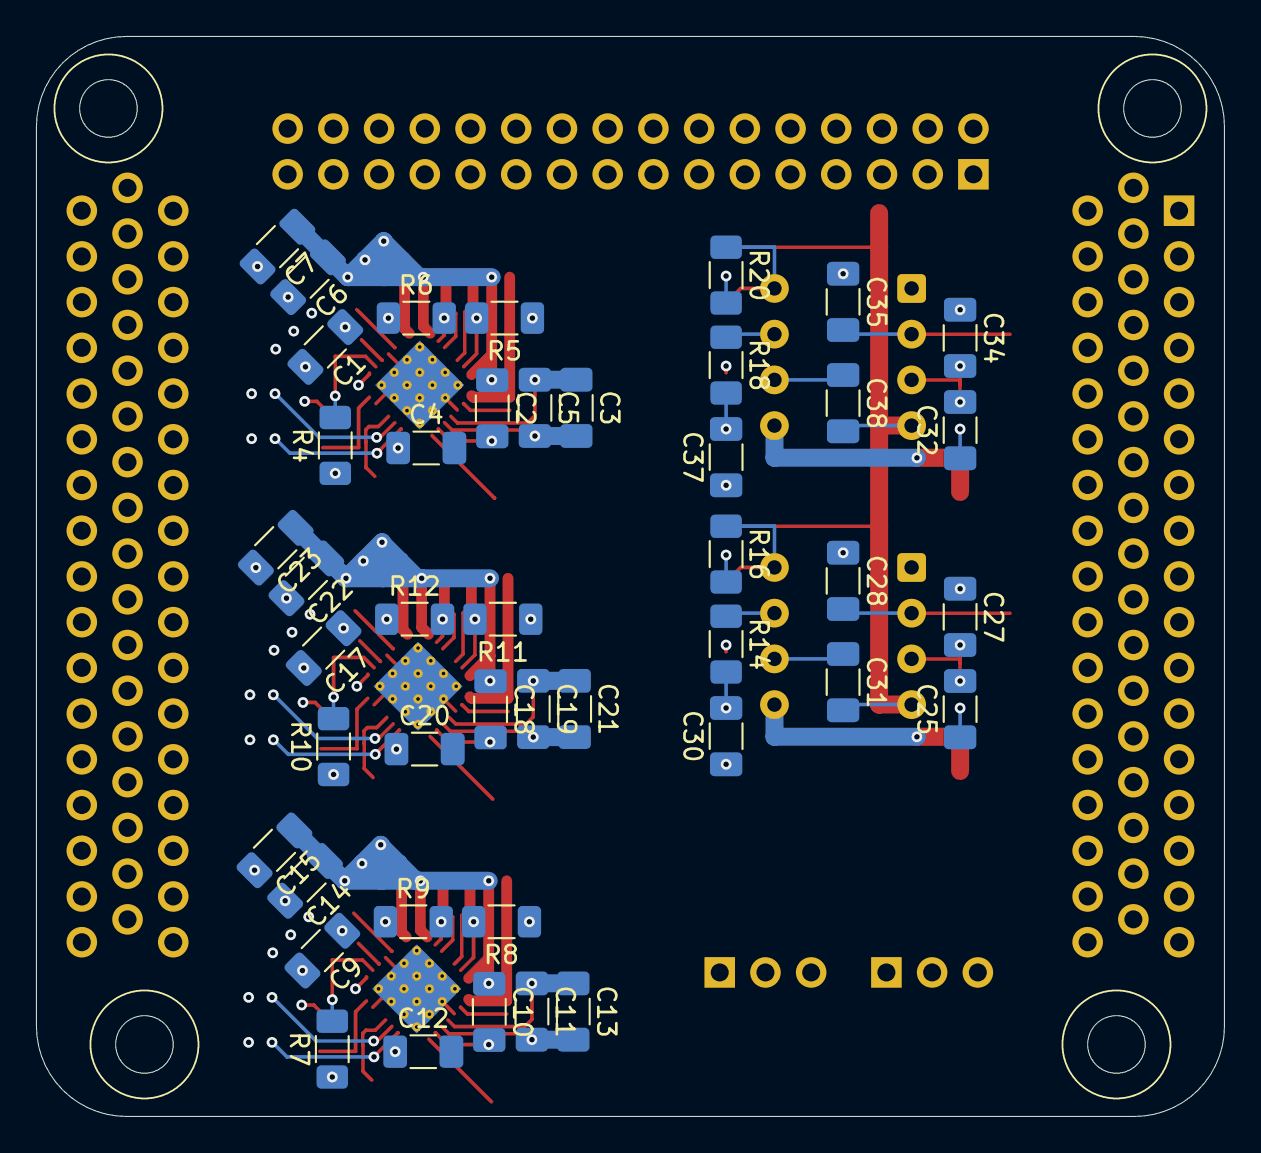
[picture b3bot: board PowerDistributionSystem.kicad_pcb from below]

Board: 4 copper layers, 66.0 x 60.0 mm, 85 parts (44 on the bottom side), 70 nets.

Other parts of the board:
N1: Housing; Dummy
